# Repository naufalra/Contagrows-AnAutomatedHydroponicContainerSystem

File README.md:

# Contagrows - An Automated Hydroponic Container System
# Project Overview

Container farms are becoming increasingly popular within the controlled environment agriculture industry. These farms are usually vertical farming systems installed inside a shipping container. The main objective is to make sure the local temperature is below 16 degrees Celcius with 80% of humidity so the plant can grow inside a controlled hygiene container. To do so, the container is equipped with AC, Fans, and an automatic watering and monitoring system.

During the manufacturing process, we had a lot of discussions with good friends from agricultural technology and PIAT (Center for Agro-Technology Innovation) UGM to produce a suitable and sustainable product.

Among our discussion topics was the system's design to meet the plant and electronic requirements. The discussion process resulted in the flow chart below

# Directory

To short things out, this is the directories of this project.

- [Article](https://www.linkedin.com/posts/naufalaryaputra_contagrow-an-automated-container-hydroponic-activity-6986608747372494849-8hf9?utm_source=share&utm_medium=member_desktop)
 - [Electrical Design](https://github.com/naufalra/Contagrows/tree/main/1.%20Electrical)
 - [Mechanical Design](https://github.com/naufalra/Contagrows/tree/main/3.%20Mechanical)
 - [Arduino Program](https://github.com/naufalra/Contagrows/tree/main/2.%20Firmware)

# Intelligent property rights

**Alat Otomasi dan Monitoring Budidaya Hidroponik**

```bash
  https://pdki-indonesia.dgip.go.id/detail/A00202203526?type=di&keyword=A00202203526 
```

**Media Tanam Pertanian Vertikal Hidroponik pada Kontainer**

```bash
 https://pdki-indonesia.dgip.go.id/detail/A00202203525?type=di&keyword=A00202203525
```

# Final Result

## Electronics System
The control system itself is using Arduino Mega2560 as the main processor. The Arduino is connected to several built in sensors like DHT11, BME280, the boards is also provide more ports for additional sensor.

## Wiring
We divided the panel into two parts to simplify the troubleshooting process and panel tidiness. 

The right panel (the one without LCD) functions as an electrical panel directly connected to the source. This panel also acts as the main switch.

The second panel only serves as the system control and automation of the tool. All control, monitoring, and automation are done through this panel. It is on this panel that the Arduino and sensors are placed.

We realize that many things can be improved in our electronic and wiring systems, but we have not had the chance to do so due to limited time. The safety process has also not been maximized because all energy has been diverted to the automation system.

## Mechanical Design
This system utilizes a 20-foot container to work. The container was chosen because it is easier to place in urban areas. Still, on the inside, we added several other components to support the needs, including plant shelves, setting panels, and screen protectors on boards to protect from water and dust.

### Shelf
The shelf is designed to accommodate approximately 1000 plant seeds placed in polybags. The rack design considers the plant seeds' maximum capacity and the container's space.

### Panel Box
The panel box is used as the setting center of the tool before the automation process takes place. In addition, on the panel, there is also a sensor reading value viewer to be monitored.

### LCD protectors
We also ad LCD protector as an additional protection for LCD from dust and water drops.

## Overall System
This is the final result of recent design

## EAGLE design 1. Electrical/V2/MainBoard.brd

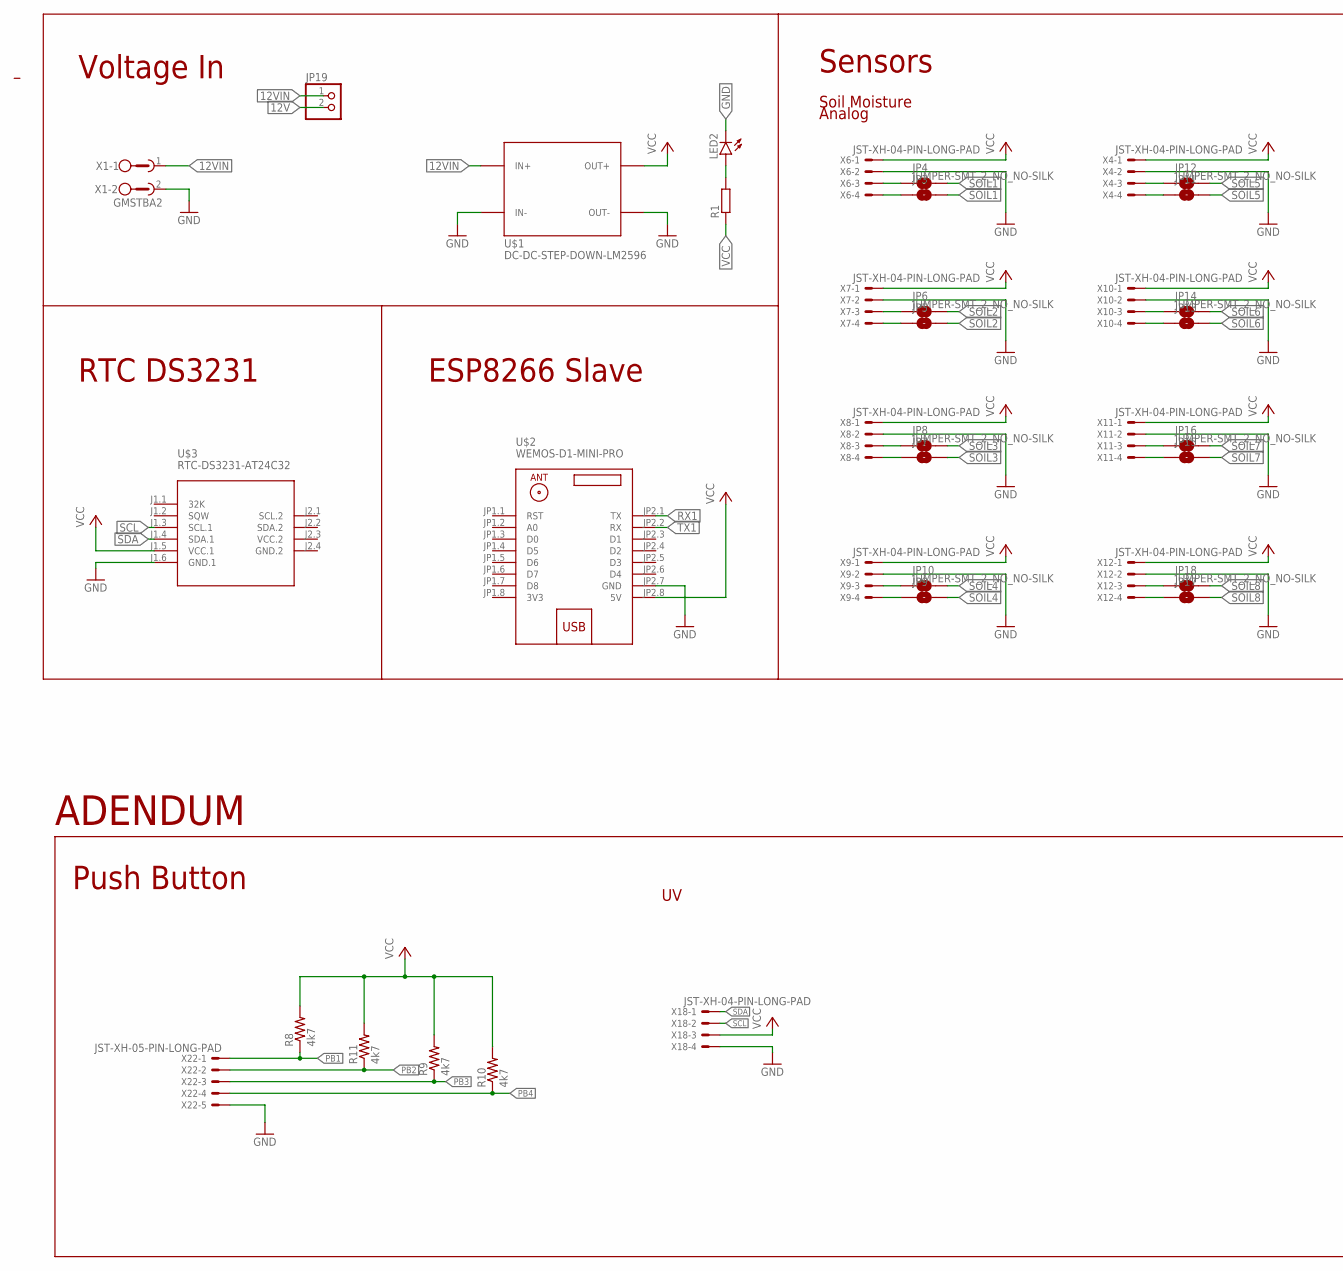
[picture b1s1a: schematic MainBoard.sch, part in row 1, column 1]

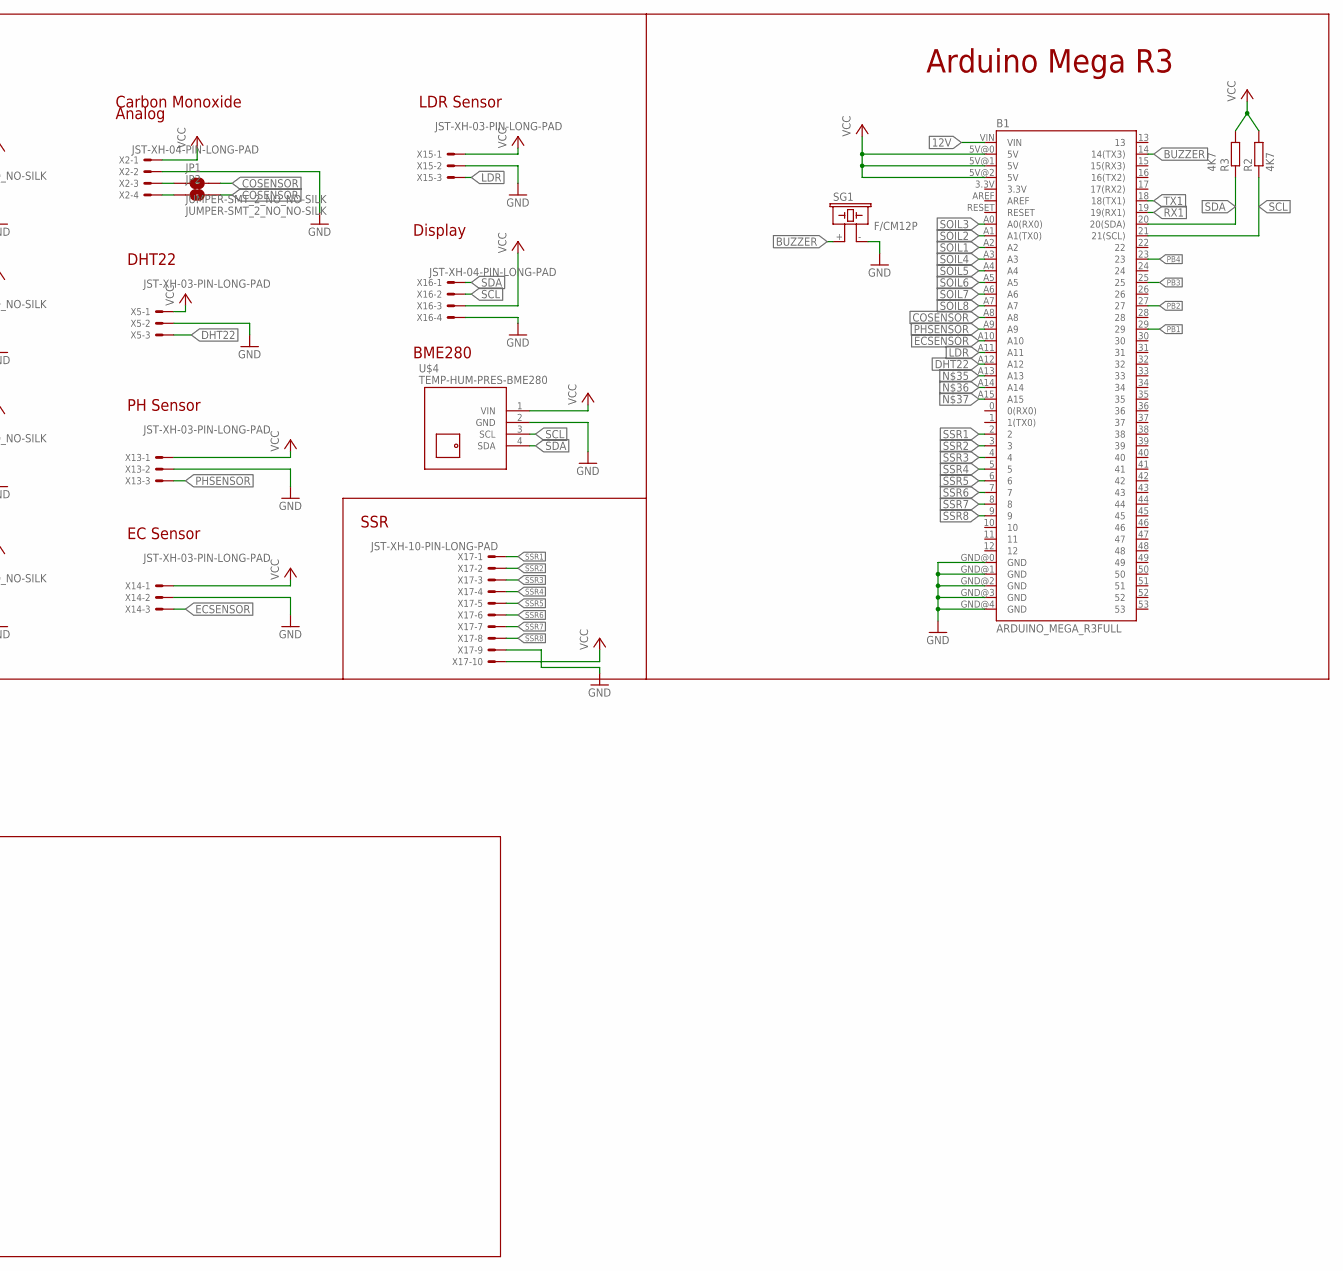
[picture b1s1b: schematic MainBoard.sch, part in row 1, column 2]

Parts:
B1: ARDUINO_MEGA_R3FULL; ARDUINO_MEGA
JP1, JP2, JP3, JP4, JP5, JP6, JP7, JP8, JP9, JP10, JP11, JP12, JP13, JP14, JP15, JP16, JP17, JP18: JUMPER-SMT_2_NO_NO-SILK; SMT-JUMPER_2_NO_NO-SILK
JP19: PINHD-1X2; 1X02
LED2: LED5MM
R1: R-EU_R0805; R0805
R2, R3: 4K7; M0805
R8, R9, R10, R11: 4k7; M0805
SG1: F/CM12P
U$1: DC-DC-STEP-DOWN-LM2596
U$2: WEMOS-D1-MINI-PRO
U$3: RTC-DS3231-AT24C32
U$4: TEMP-HUM-PRES-BME280
X1: GMSTBA2
X2, X4, X6, X7, X8, X9, X10, X11, X12, X16, X18: JST-XH-04-PIN-LONG-PAD; JST-XH-04-PACKAGE-LONG-PAD
X5, X13, X14, X15: JST-XH-03-PIN-LONG-PAD; JST-XH-03-PACKAGE-LONG-PAD
X17: JST-XH-10-PIN-LONG-PAD; JST-XH-10-PACKAGE-LONG-PAD
X22: JST-XH-05-PIN-LONG-PAD; JST-XH-05-PACKAGE-LONG-PAD

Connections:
3V3: U$2.JP1.8 (3V3)
12V: B1.VIN, JP19.2
12VIN: JP19.1, U$1.IN+, X1.1
BUZZER: B1.14 (14(TX3)), SG1.+ (1)
COSENSOR: B1.A8, JP1.2, JP2.2
DHT22: B1.A12, X5.3
ECSENSOR: B1.A10, X14.3
GND: B1.GND@0 (GND), B1.GND@1 (GND), B1.GND@2 (GND), B1.GND@3 (GND), B1.GND@4 (GND), LED2.K (C), SG1.- (2), U$1.IN-, U$1.OUT-, U$2.JP2.7 (GND), U$3.J1.6 (GND.1), U$4.2 (GND), X1.2, X2.2, X4.2, X5.2, X6.2, X7.2, X8.2, X9.2, X10.2, X11.2, X12.2, X13.2, X14.2, X15.2, X16.4, X17.9, X18.4, X22.5
GND.2: U$3.J2.4 (GND.2)
LDR: B1.A11, X15.3
unnamed: JP1.1, X2.3
unnamed: JP2.1, X2.4
unnamed: JP3.1, X6.4
unnamed: JP4.1, X6.3
unnamed: LED2.A, R1.2
unnamed: JP5.1, X7.4
unnamed: JP6.1, X7.3
unnamed: JP7.1, X8.4
unnamed: JP8.1, X8.3
unnamed: JP9.1, X9.4
unnamed: JP10.1, X9.3
unnamed: JP11.1, X4.4
unnamed: JP12.1, X4.3
unnamed: JP13.1, X10.4
unnamed: JP14.1, X10.3
unnamed: JP15.1, X11.4
unnamed: JP16.1, X11.3
unnamed: JP17.1, X12.4
unnamed: JP18.1, X12.3
PB1: B1.29, R8.1, X22.1
PB2: B1.27, R11.1, X22.2
PB3: B1.25, R9.1, X22.3
PB4: B1.23, R10.1, X22.4
PHSENSOR: B1.A9, X13.3
RX1: B1.19 (19(RX1)), U$2.JP2.1 (TX)
SCL: B1.21 (21(SCL)), R2.1, U$3.J1.3 (SCL.1), U$4.3 (SCL), X16.2, X18.2
SDA: B1.20 (20(SDA)), R3.1, U$3.J1.4 (SDA.1), U$4.4 (SDA), X16.1, X18.1
SOIL1: B1.A2, JP3.2, JP4.2
SOIL2: B1.A1 (A1(TX0)), JP5.2, JP6.2
SOIL3: B1.A0 (A0(RX0)), JP7.2, JP8.2
SOIL4: B1.A3, JP9.2, JP10.2
SOIL5: B1.A4, JP11.2, JP12.2
SOIL6: B1.A5, JP13.2, JP14.2
SOIL7: B1.A6, JP15.2, JP16.2
SOIL8: B1.A7, JP17.2, JP18.2
SSR1: B1.2, X17.1
SSR2: B1.3, X17.2
SSR3: B1.4, X17.3
SSR4: B1.5, X17.4
SSR5: B1.6, X17.5
SSR6: B1.7, X17.6
SSR7: B1.8, X17.7
SSR8: B1.9, X17.8
TX1: B1.18 (18(TX1)), U$2.JP2.2 (RX)
VCC: B1.5V@0 (5V), B1.5V@1 (5V), B1.5V@2 (5V), R1.1, R2.2, R3.2, R8.2, R9.2, R10.2, R11.2, U$1.OUT+, U$2.JP2.8 (5V), U$3.J1.5 (VCC.1), U$4.1 (VIN), X2.1, X4.1, X5.1, X6.1, X7.1, X8.1, X9.1, X10.1, X11.1, X12.1, X13.1, X14.1, X15.1, X16.3, X17.10, X18.3
VCC.2: U$3.J2.3 (VCC.2)

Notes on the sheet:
Voltage In
Arduino Mega R3
RTC DS3231
ESP8266 Slave
Sensors
Carbon Monoxide
DHT22
Soil Moisture
PH Sensor
EC Sensor
Analog
LDR Sensor
Display
BME280
SSR
Push Button
ADENDUM

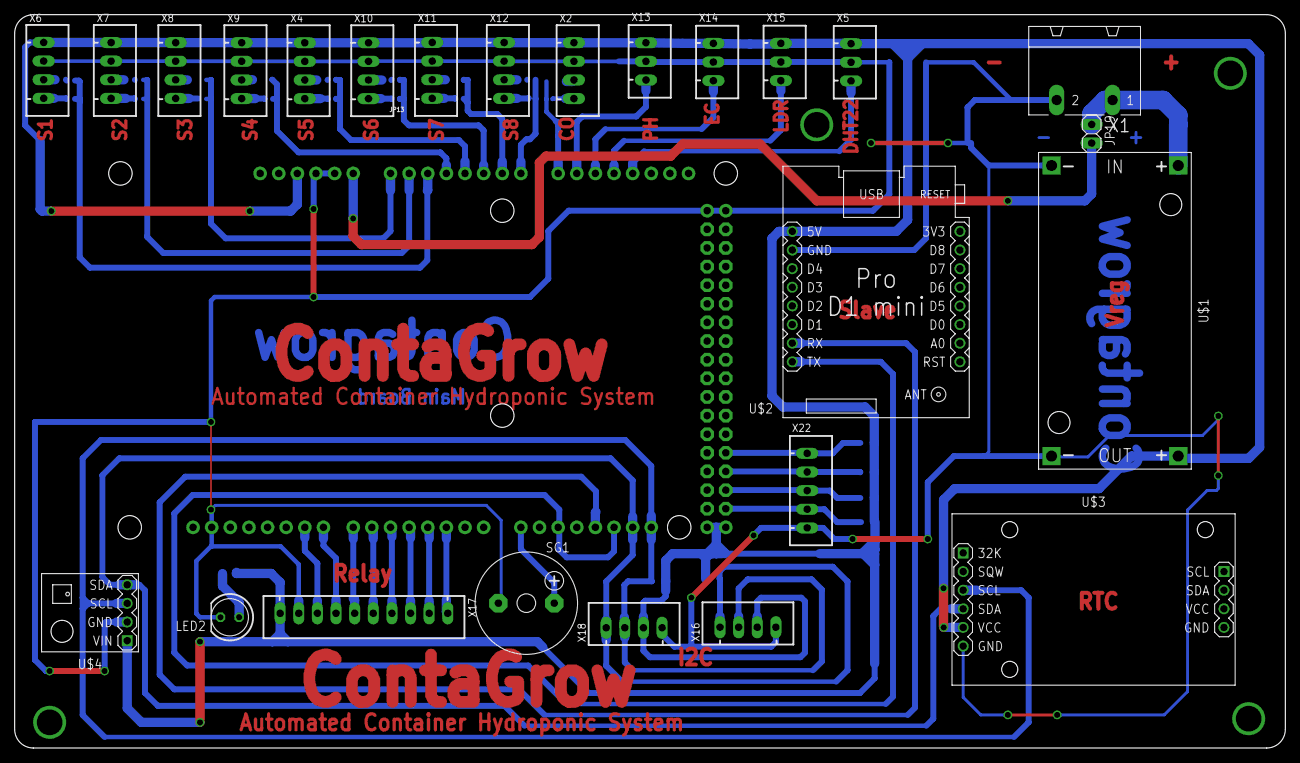
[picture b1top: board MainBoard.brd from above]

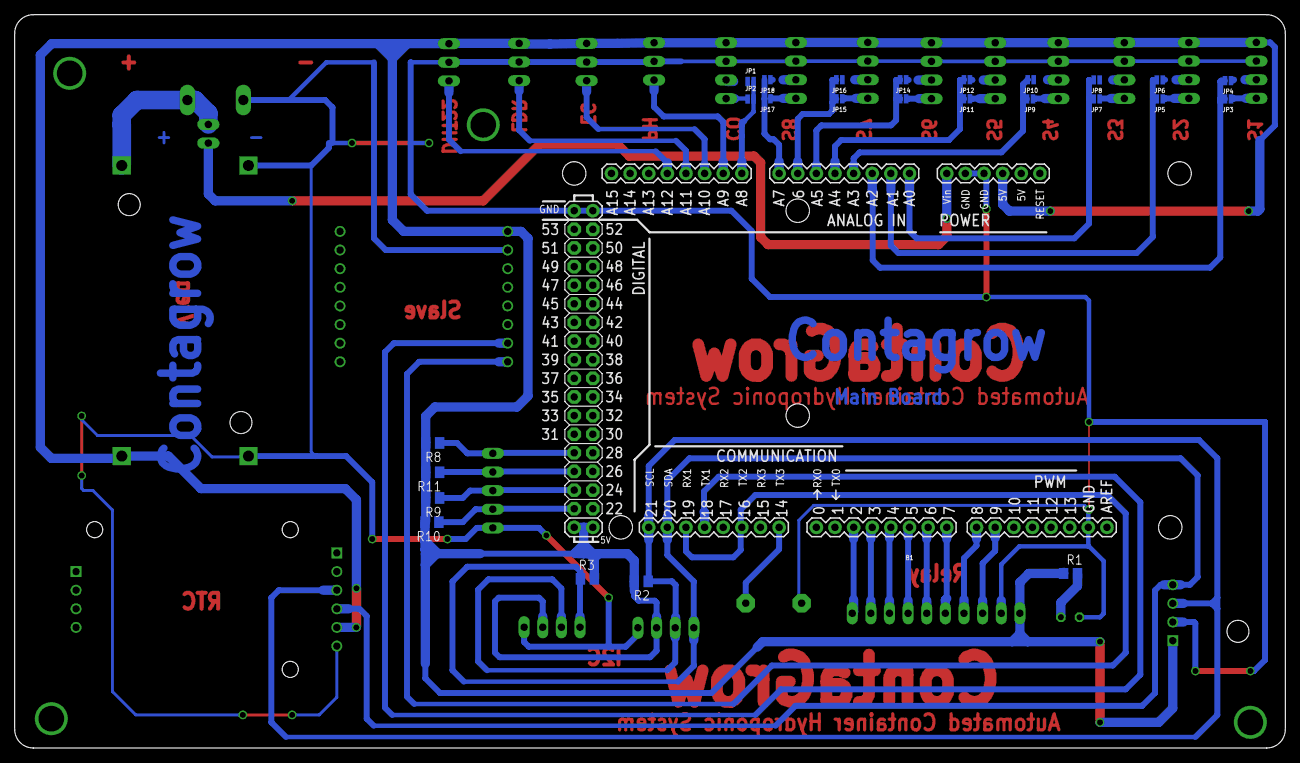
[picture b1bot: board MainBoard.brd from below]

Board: 2 copper layers, 173.3 x 100.0 mm, 51 parts (26 on the bottom side), 53 nets.

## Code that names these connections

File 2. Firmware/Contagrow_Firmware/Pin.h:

#define     COPIN           A8 //kanan
#define     DHTPIN          A9
#define     PHSensor        A12 //kanan
#define     ECSensor        A10


#define     SOIL1           A2//kanan
#define     SOIL2           A1
#define     SOIL3           A0 //kanan
#define     SOIL4           A3
#define     SOIL5           A4 //kanan
#define     SOIL6           A5
#define     SOIL7           A6 //kanan
#define     SOIL8           A7

#define     Relay1          2//kanan
#define     Relay2          3
#define     Relay3          4 //kanan
#define     Relay4          5
#define     Relay5          6 //kanan
#define     Relay6          7
#define     Relay7          8
#define     Relay8          9

#define     button1         29 //Paling kanan
#define     button2         27
#define     button3         25
#define     button4         23 //Paling Kiri

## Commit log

2023-04-25 Final version
    Tidy up some stuff
    Final version of readme are added.
    Many thanks for all of the team involved
2023-04-25 Some Private docs are removed
2023-04-26 Real Pict added, HKI is rearranged
2023-04-26 Minor update
2023-04-26 minor update fixed

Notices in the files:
parts and their libraries:
SparkFun-Boards: Licensing: Creative Commons ShareAlike 4.0 International - https://creativecommons.org/licenses/by-sa/4.0
diy-modules: Released under the Creative Commons Attribution 4.0 International License: http://creativecommons.org/licenses/by/4.0
